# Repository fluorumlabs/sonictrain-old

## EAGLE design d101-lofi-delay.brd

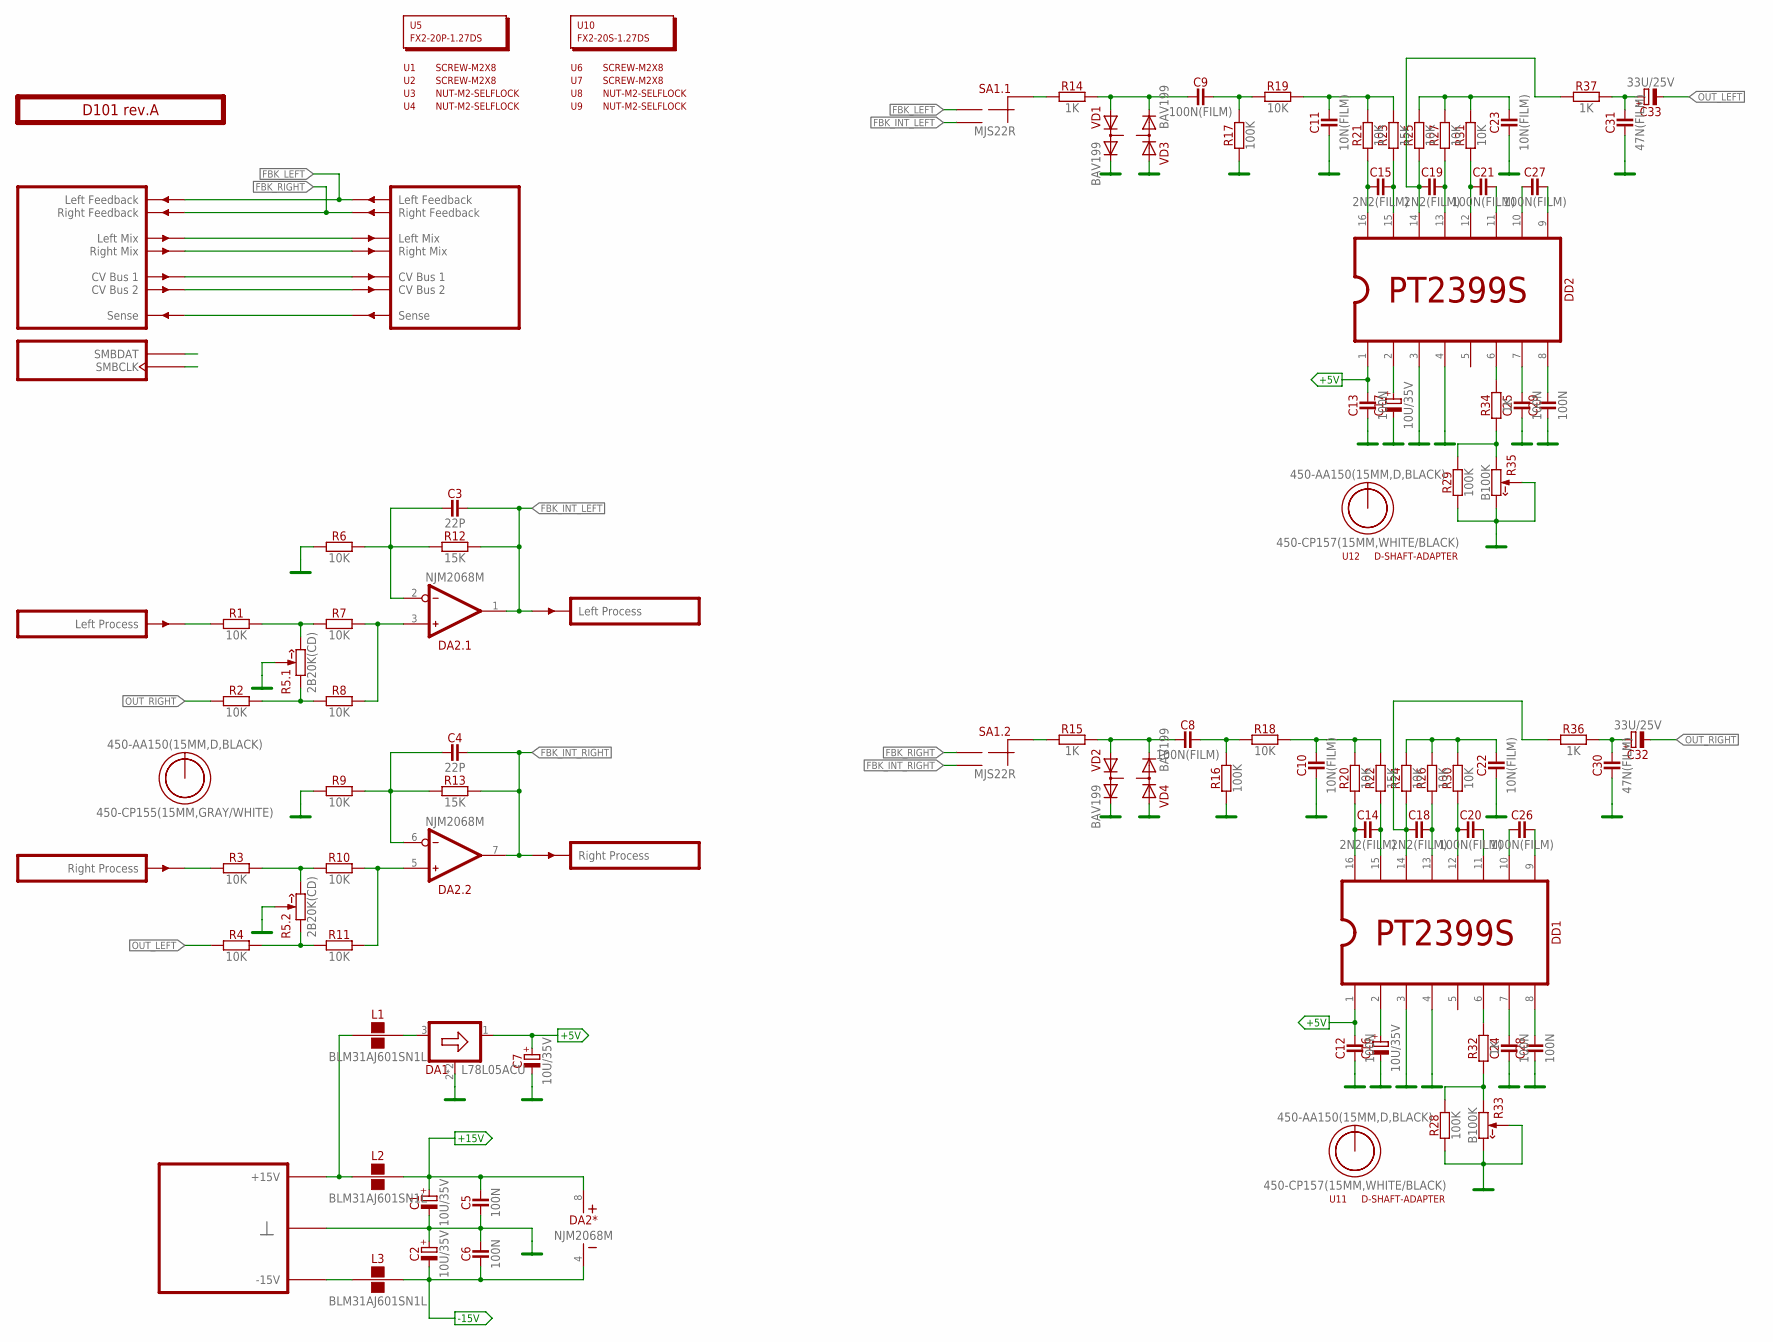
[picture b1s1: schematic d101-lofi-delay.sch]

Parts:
C1, C2, C7, C16, C17: 10U/35V; E2-5
C3, C4: 22P; C-0805
C5, C6, C12, C13, C24, C25, C28, C29: 100N; C-0805
C8, C9, C20, C21, C26, C27: 100N(FILM); C050-025X075
C10, C11, C22, C23: 10N(FILM); C050-025X075
C14, C15, C18, C19: 2N2(FILM); C050-025X075
C30, C31: 47N(FILM); C050-025X075
C32, C33: 33U/25V; E2,5-7
DA1: L78L05ACU; SOT89
DA2: NJM2068M; SO-8
DD1, DD2: PT2399S; SO-16; PARTNO *
L1, L2, L3: BLM31AJ601SN1L; 1206
O1, O3, O5: 450-AA150(15MM,D,BLACK); EMPTY
O2: 450-CP155(15MM,GRAY/WHITE); EMPTY
O4, O6: 450-CP157(15MM,WHITE/BLACK); EMPTY
PCB1: D101 rev.A; ST2-BOARD-50
R1, R2, R3, R4, R6, R7, R8, R9, R10, R11, R18, R19, R20, R21, R24, R25, R26, R27, R30, R31: 10K; R-0805
R5: 2B20K(CD); RV11-DUAL
R12, R13, R22, R23: 15K; R-0805
R14, R15, R32, R34, R36, R37: 1K; R-0805
R16, R17, R28, R29: 100K; R-0805
R33, R35: B100K; RV11-SINGLE
SA1: MJS22R; APEM-MJS22R
U1, U2, U6, U7: SCREW-M2X8; EMPTY
U3, U4, U8, U9: NUT-M2-SELFLOCK; EMPTY
U5: FX2-20P-1.27DS; EMPTY
U10: FX2-20S-1.27DS; EMPTY
U11, U12: D-SHAFT-ADAPTER; EMPTY
VD1, VD2, VD3, VD4: BAV199; SOT23

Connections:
+5V: C7.+, C12.2, C13.2, DA1.1 (OUT), DD1.1, DD2.1
+15V: C1.+, C5.2, DA2.8 (V+), L2.2
-15V: C2.-, C6.1, DA2.4 (V-), L3.2
FBK_INT_LEFT: C3.2, DA2.1 (OUT), PCB1.BOUTL' (OUTL), R12.2, SA1.NO1 (2)
FBK_INT_RIGHT: C4.2, DA2.7 (OUT), PCB1.BOUTR' (OUTR), R13.2, SA1.NO2 (2)
FBK_LEFT: PCB1.ALFBK (LFBK), PCB1.ALFBK' (LFBK'), SA1.NC1 (1)
FBK_RIGHT: PCB1.ARFBK (RFBK), PCB1.ARFBK' (RFBK'), SA1.NC2 (1)
GND: C1.-, C2.+, C5.1, C6.2, C7.-, C10.1, C11.1, C12.1, C13.1, C16.-, C17.-, C22.1, C23.1, C24.1, C25.1, C28.1, C29.1, C30.1, C31.1, DA1.2 (GND), DA1.2@1 (GND), DD1.3, DD1.4, DD2.3, DD2.4, PCB1.B4 (GND), PCB1.B4' (GND), PCB1.B5 (GND), PCB1.B5' (GND), PCB1.B6 (GND), PCB1.B6' (GND), PCB1.B7 (GND), PCB1.B7' (GND), PCB1.B8 (GND), PCB1.B8' (GND), R5.2 (W), R5.2' (W), R6.1, R9.1, R16.1, R17.1, R28.1, R29.1, R33.2 (W), R33.3 (CW), R35.2 (W), R35.3 (CW), VD1.2 (C), VD2.2 (C), VD3.1 (A), VD4.1 (A)
LMIX: PCB1.ALMIX (LMIX), PCB1.ALMIX' (LMIX')
unnamed: R29.2, R34.1, R35.1 (CCW)
unnamed: R28.2, R32.1, R33.1 (CCW)
unnamed: C9.1, R14.2, VD1.1 (A), VD3.2 (C)
unnamed: C15.1, DD2.16, R21.1
unnamed: C8.1, R15.2, VD2.1 (A), VD4.2 (C)
unnamed: R14.1, SA1.C1 (CM)
unnamed: R3.2, R5.3' (CW), R10.1
unnamed: C9.2, R17.2, R19.1
unnamed: C11.2, R19.2, R21.2, R23.2
unnamed: PCB1.BINL (INL), R1.1
unnamed: R15.1, SA1.C2 (CM)
unnamed: C23.2, R25.2, R27.2, R31.2
unnamed: PCB1.BSENSE (SENSE), PCB1.BSENSE' (SENSE')
unnamed: C15.2, DD2.15, R23.1
unnamed: C19.1, DD2.14, R25.1, R37.1
unnamed: C19.2, DD2.13, R27.1
unnamed: C21.1, DD2.12, R31.1
unnamed: C21.2, DD2.11
unnamed: C27.1, DD2.10
unnamed: C27.2, DD2.9
unnamed: C31.2, C33.+, R37.2
unnamed: C4.1, DA2.6 (IN-), R9.2, R13.1
unnamed: PCB1.BINR (INR), R3.1
unnamed: R1.2, R5.3 (CW), R7.1
unnamed: C25.2, DD2.7
unnamed: C29.2, DD2.8
unnamed: DD2.6, R34.2
unnamed: L3.1, PCB1.A-15 (P-15V), PCB1.A-15' (P-15V), PCB1.B-15 (P-15V), PCB1.B-15' (P-15V)
unnamed: C17.+, DD2.2
unnamed: PCB1.ASMBDAT (SMBDAT), PCB1.ASMBDAT' (SMBDAT)
unnamed: DA2.5 (IN+), R10.2, R11.2
unnamed: R4.2, R5.1' (CCW), R11.1
unnamed: PCB1.ACV1 (CV1), PCB1.ACV1' (CV1')
unnamed: PCB1.ACV2 (CV2), PCB1.ACV2' (CV2')
unnamed: PCB1.ASMBCLK (SMBCLK), PCB1.ASMBCLK' (SMBCLK)
unnamed: DA1.3 (IN), L1.2
unnamed: C22.2, R24.2, R26.2, R30.2
unnamed: C14.1, DD1.16, R20.1
unnamed: C14.2, DD1.15, R22.1
unnamed: C18.1, DD1.14, R24.1, R36.1
unnamed: C18.2, DD1.13, R26.1
unnamed: C20.1, DD1.12, R30.1
unnamed: C20.2, DD1.11
unnamed: C26.1, DD1.10
unnamed: C26.2, DD1.9
unnamed: C30.2, C32.+, R36.2
unnamed: C24.2, DD1.7
unnamed: C28.2, DD1.8
unnamed: DD1.6, R32.2
unnamed: DA2.3 (IN+), R7.2, R8.2
unnamed: C8.2, R16.2, R18.1
unnamed: C10.2, R18.2, R20.2, R22.2
unnamed: C3.1, DA2.2 (IN-), R6.2, R12.1
unnamed: R2.2, R5.1 (CCW), R8.1
unnamed: C16.+, DD1.2
OUT_LEFT: C33.-, R4.1
OUT_RIGHT: C32.-, R2.1
P+15V: L1.1, L2.1, PCB1.A+15 (P+15V), PCB1.A+15' (P+15V), PCB1.B+15 (P+15V), PCB1.B+15' (P+15V)
RMIX: PCB1.ARMIX (RMIX), PCB1.ARMIX' (RMIX')

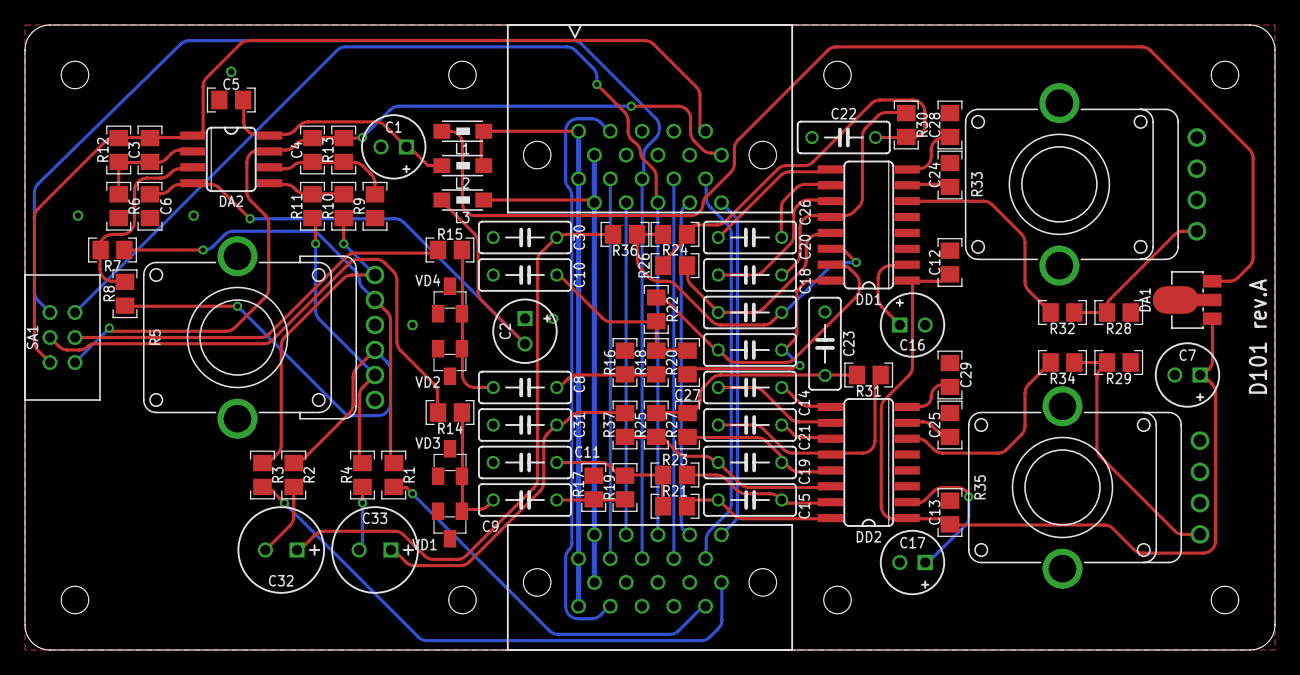
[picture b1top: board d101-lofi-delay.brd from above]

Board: 2 copper layers, 100.0 x 50.0 mm, 101 parts (0 on the bottom side), 68 nets.

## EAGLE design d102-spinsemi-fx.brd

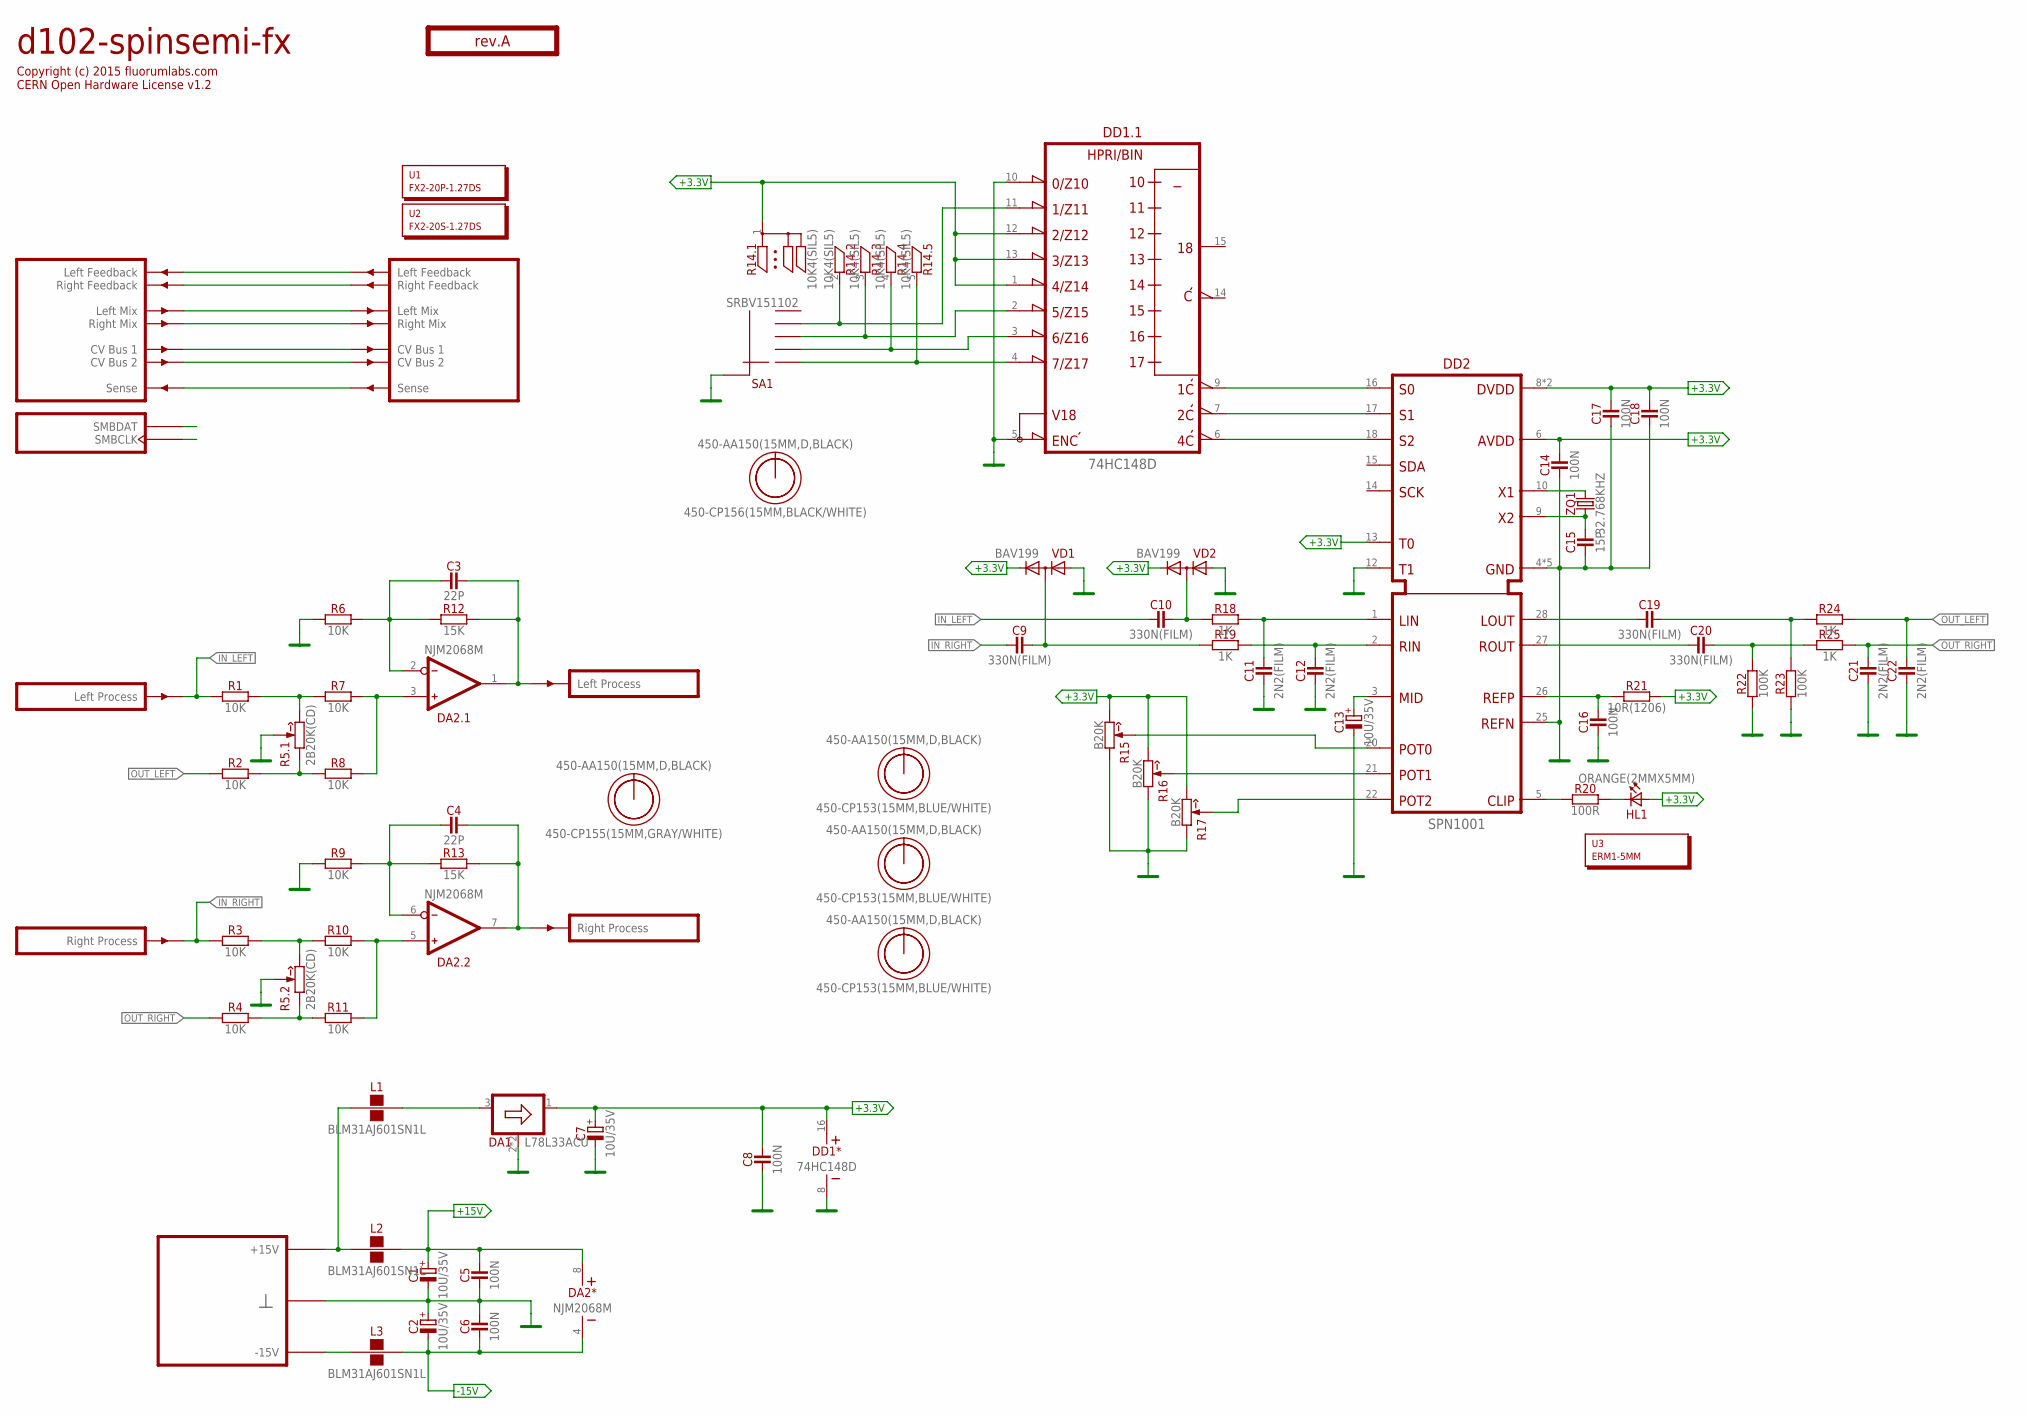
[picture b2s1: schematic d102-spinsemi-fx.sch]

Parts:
C1, C2, C7, C13: 10U/35V; E2-5
C3, C4: 22P; C-0805
C5, C6, C8, C14, C16, C17, C18: 100N; C-0805
C9, C10, C19, C20: 330N(FILM); C050-035X075
C11, C12, C21, C22: 2N2(FILM); C050-025X075
C15: 15P; C-0805
DA1: L78L33ACU; SOT89
DA2: NJM2068M; SO-8
DD1: 74HC148D; SO-16
DD2: SPN1001; SO28W
HL1: ORANGE(2MMX5MM); LED2X5
L1, L2, L3: BLM31AJ601SN1L; 1206
O1: TITLE; EMPTY
O2, O4, O6, O8, O10: 450-AA150(15MM,D,BLACK); EMPTY
O3: 450-CP155(15MM,GRAY/WHITE); EMPTY
O5: 450-CP156(15MM,BLACK/WHITE); EMPTY
O7, O9, O11: 450-CP153(15MM,BLUE/WHITE); EMPTY
PCB1: rev.A; ST2-BOARD-50
R1, R2, R3, R4, R6, R7, R8, R9, R10, R11: 10K; R-0805
R5: 2B20K(CD); RV11-DUAL
R12, R13: 15K; R-0805
R14: 10K4(SIL5); R-SIL5
R15, R16, R17: B20K; RV11-SINGLE
R18, R19, R24, R25: 1K; R-0805
R20: 100R; R-0805
R21: 10R(1206); R-1206
R22, R23: 100K; R-0805
SA1: SRBV151102; SRBV
U1: FX2-20P-1.27DS; EMPTY
U2: FX2-20S-1.27DS; EMPTY
U3: ERM1-5MM; EMPTY
VD1, VD2: BAV199; SOT23
ZQ1: 32.768KHZ; 3215

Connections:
+3.3V: C7.+, C8.2, C14.2, C17.2, C18.2, DA1.1 (OUT), DD1.1 (4), DD1.12 (2), DD1.13 (3), DD1.16 (V+), DD2.6 (AVDD), DD2.8 (DVDD), DD2.13 (T0), DD2.23 (DVDD), HL1.A, R14.1, R15.3 (CW), R16.3 (CW), R17.3 (CW), R21.2, VD1.2 (C), VD2.2 (C)
+15V: C1.+, C5.2, DA2.8 (V+), L2.2
-15V: C2.-, C6.1, DA2.4 (V-), L3.2
GND: C1.-, C2.+, C5.1, C6.2, C7.-, C8.1, C11.1, C12.1, C13.-, C14.1, C15.1, C16.1, C17.1, C18.1, C21.1, C22.1, DA1.2 (GND), DA1.2@1 (GND), DD1.5 (EI), DD1.8 (V-), DD1.10 (0), DD2.4 (GND), DD2.7 (GND), DD2.11 (GND), DD2.12 (T1), DD2.19 (GND), DD2.24 (GND), DD2.25 (REFN), PCB1.B4 (GND), PCB1.B4' (GND), PCB1.B5 (GND), PCB1.B5' (GND), PCB1.B6 (GND), PCB1.B6' (GND), PCB1.B7 (GND), PCB1.B7' (GND), PCB1.B8 (GND), PCB1.B8' (GND), R5.2 (W), R5.2' (W), R6.1, R9.1, R15.1 (CCW), R16.1 (CCW), R17.1 (CCW), R22.1, R23.1, SA1.1 (CM), SA1.10 (CM), VD1.1 (A), VD2.1 (A)
IN_LEFT: C10.1, PCB1.BINL (INL), R1.1
IN_RIGHT: C9.1, PCB1.BINR (INR), R3.1
LMIX: PCB1.ALMIX (LMIX), PCB1.ALMIX' (LMIX')
unnamed: PCB1.ALFBK (LFBK), PCB1.ALFBK' (LFBK')
unnamed: PCB1.ARFBK (RFBK), PCB1.ARFBK' (RFBK')
unnamed: C3.2, DA2.1 (OUT), PCB1.BOUTL' (OUTL), R12.2
unnamed: C4.2, DA2.7 (OUT), PCB1.BOUTR' (OUTR), R13.2
unnamed: DD1.4 (7), R14.5, SA1.2 (1)
unnamed: DD1.3 (6), R14.4, SA1.3 (2)
unnamed: R3.2, R5.3' (CW), R10.1
unnamed: DD1.2 (5), R14.3, SA1.4 (3)
unnamed: DD1.11 (1), R14.2, SA1.5 (4)
unnamed: DD1.9 (A0), DD2.16 (S0)
unnamed: DD2.10 (X1), ZQ1.2
unnamed: DD1.7 (A1), DD2.17 (S1)
unnamed: DD1.6 (A2), DD2.18 (S2)
unnamed: HL1.K (C), R20.2
unnamed: DD2.5 (CLIP), R20.1
unnamed: PCB1.BSENSE (SENSE), PCB1.BSENSE' (SENSE')
unnamed: C12.2, DD2.2 (RIN), R19.2
unnamed: DD2.22 (POT2), R17.2 (W)
unnamed: DD2.21 (POT1), R16.2 (W)
unnamed: DD2.20 (POT0), R15.2 (W)
unnamed: C16.2, DD2.26 (REFP), R21.1
unnamed: C13.+, DD2.3 (MID)
unnamed: C11.2, DD2.1 (LIN), R18.2
unnamed: C10.2, R18.1, VD2.3 (CMN)
unnamed: C4.1, DA2.6 (IN-), R9.2, R13.1
unnamed: C9.2, R19.1, VD1.3 (CMN)
unnamed: C19.1, DD2.28 (LOUT)
unnamed: C15.2, DD2.9 (X2), ZQ1.1
unnamed: C20.1, DD2.27 (ROUT)
unnamed: R1.2, R5.3 (CW), R7.1
unnamed: C20.2, R22.2, R25.1
unnamed: C19.2, R23.2, R24.1
unnamed: L3.1, PCB1.A-15 (P-15V), PCB1.A-15' (P-15V), PCB1.B-15 (P-15V), PCB1.B-15' (P-15V)
unnamed: PCB1.ASMBDAT (SMBDAT), PCB1.ASMBDAT' (SMBDAT)
unnamed: DA2.5 (IN+), R10.2, R11.2
unnamed: R4.2, R5.1' (CCW), R11.1
unnamed: PCB1.ACV1 (CV1), PCB1.ACV1' (CV1')
unnamed: PCB1.ACV2 (CV2), PCB1.ACV2' (CV2')
unnamed: PCB1.ASMBCLK (SMBCLK), PCB1.ASMBCLK' (SMBCLK)
unnamed: DA1.3 (IN), L1.2
unnamed: DA2.3 (IN+), R7.2, R8.2
unnamed: C3.1, DA2.2 (IN-), R6.2, R12.1
unnamed: R2.2, R5.1 (CCW), R8.1
OUT_LEFT: C22.2, R2.1, R24.2
OUT_RIGHT: C21.2, R4.1, R25.2
P+15V: L1.1, L2.1, PCB1.A+15 (P+15V), PCB1.A+15' (P+15V), PCB1.B+15 (P+15V), PCB1.B+15' (P+15V)
RMIX: PCB1.ARMIX (RMIX), PCB1.ARMIX' (RMIX')

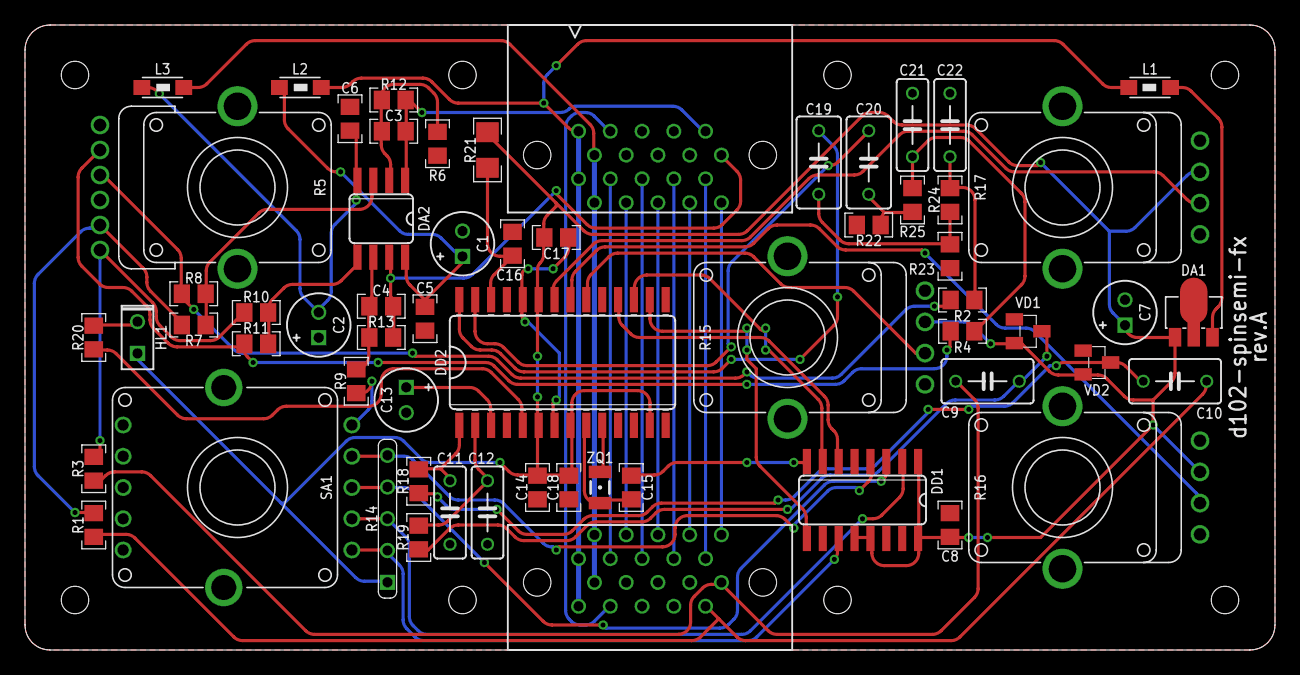
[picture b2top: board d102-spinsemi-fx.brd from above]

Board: 2 copper layers, 100.0 x 50.0 mm, 74 parts (0 on the bottom side), 54 nets.

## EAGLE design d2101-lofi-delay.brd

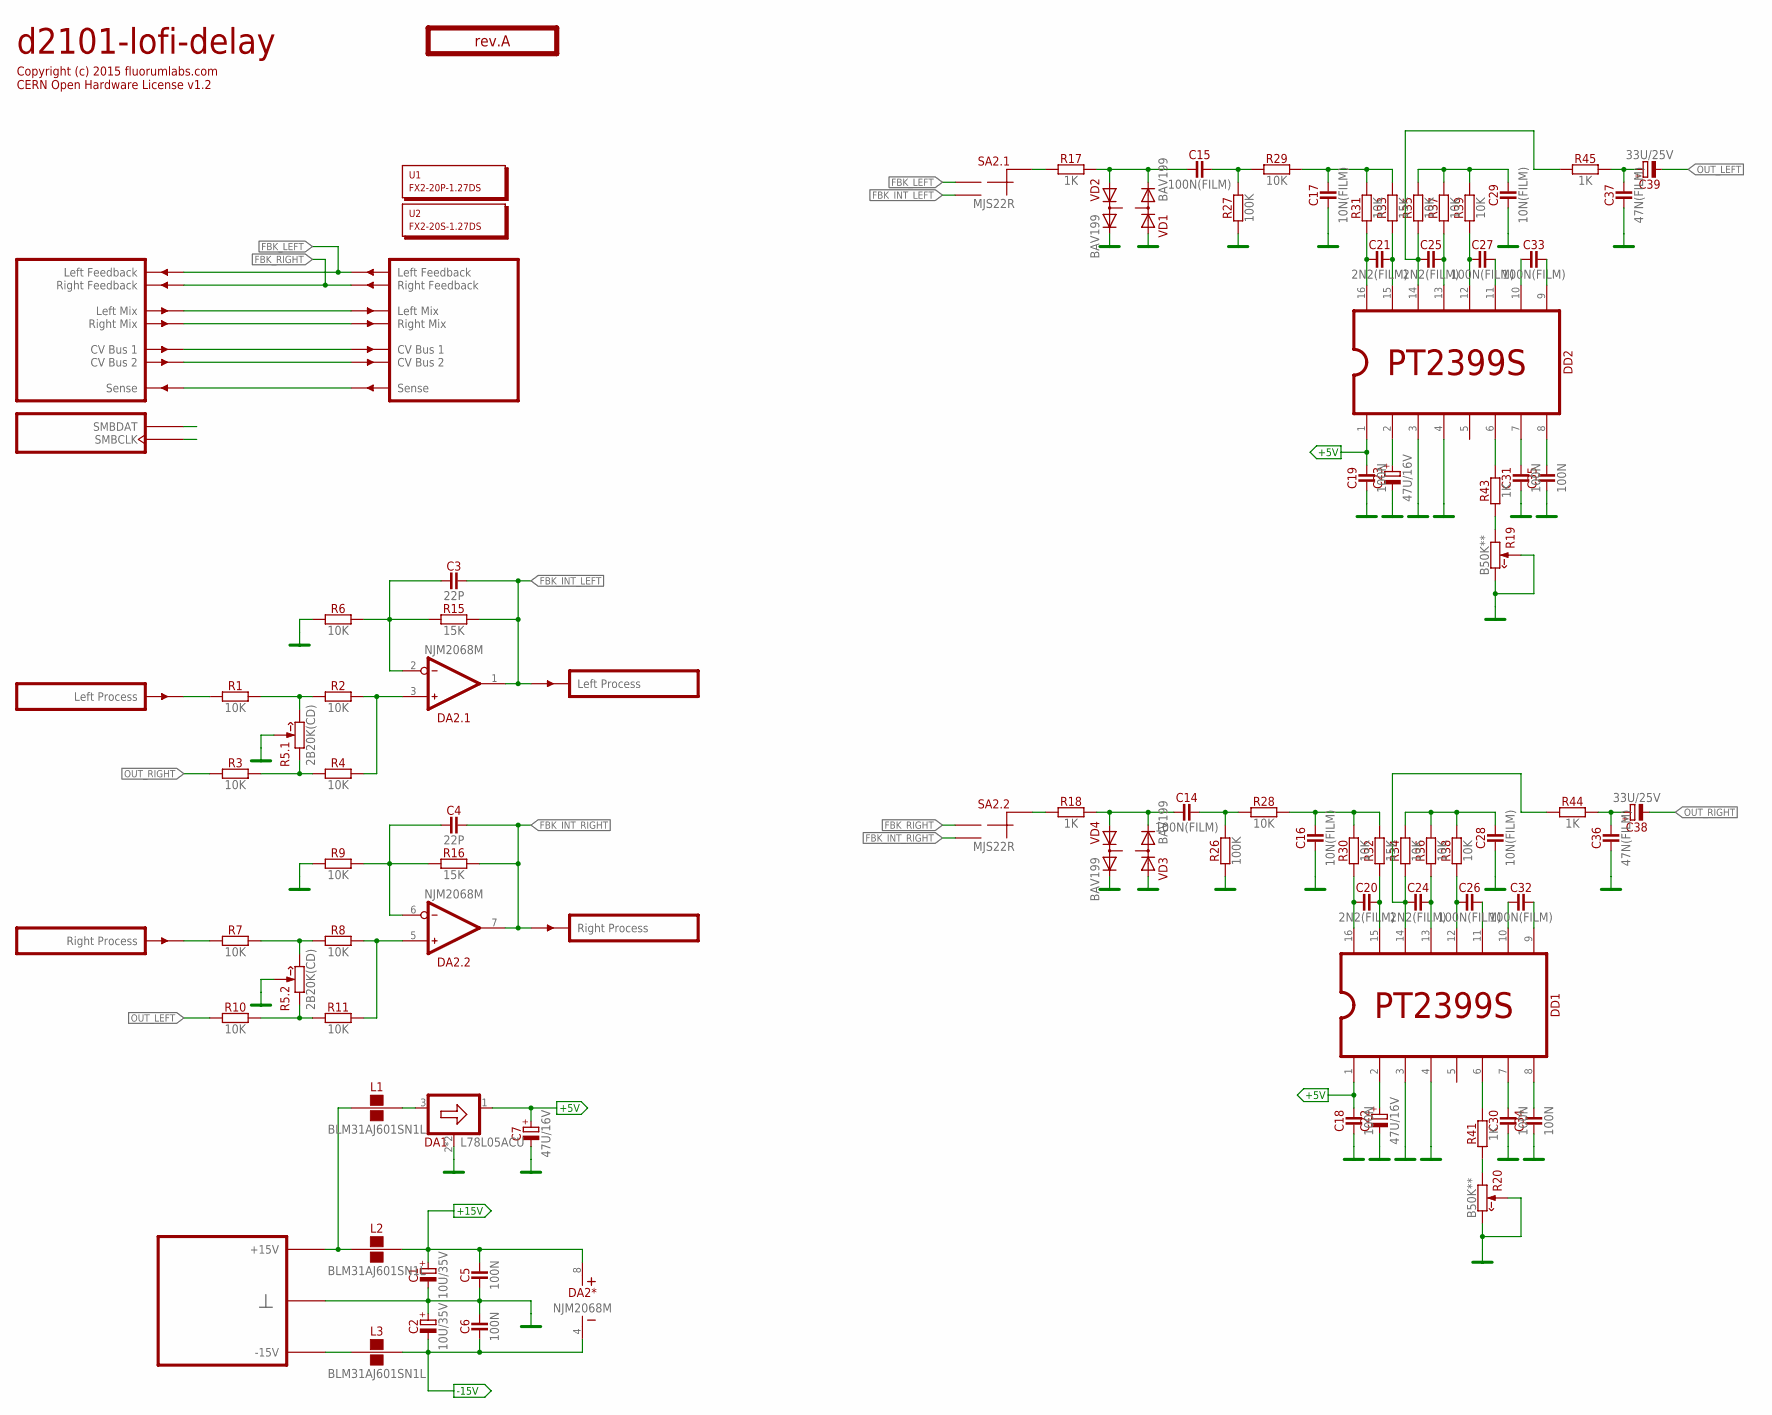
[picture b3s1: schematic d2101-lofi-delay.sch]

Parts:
C1, C2: 10U/35V; E2-5
C3, C4: 22P; C-0805
C5, C6, C18, C19, C30, C31, C34, C35: 100N; C-0805
C7, C22, C23: 47U/16V; E2-5
C14, C15, C26, C27, C32, C33: 100N(FILM); C050-025X075
C16, C17, C28, C29: 10N(FILM); C050-025X075
C20, C21, C24, C25: 2N2(FILM); C050-025X075
C36, C37: 47N(FILM); C050-025X075
C38, C39: 33U/25V; E2,5-7
DA1: L78L05ACU; SOT89
DA2: NJM2068M; SO-8
DD1, DD2: PT2399S; SO-16; PARTNO *
L1, L2, L3: BLM31AJ601SN1L; 1206
O1: TITLE; EMPTY
PCB1: rev.A; ST2-BOARD-50
R1, R2, R3, R4, R6, R7, R8, R9, R10, R11, R28, R29, R30, R31, R34, R35, R36, R37, R38, R39: 10K; R-0805
R5: 2B20K(CD); RV11-DUAL
R15, R16, R32, R33: 15K; R-0805
R17, R18, R41, R43, R44, R45: 1K; R-0805
R19, R20: B50K**; RV11-SINGLE
R26, R27: 100K; R-0805
SA2: MJS22R; APEM-MJS22R
U1: FX2-20P-1.27DS; EMPTY
U2: FX2-20S-1.27DS; EMPTY
VD1, VD2, VD3, VD4: BAV199; SOT23

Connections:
+5V: C7.+, C18.2, C19.2, DA1.1 (OUT), DD1.1, DD2.1
+15V: C1.+, C5.2, DA2.8 (V+), L2.2
-15V: C2.-, C6.1, DA2.4 (V-), L3.2
FBK_INT_LEFT: C3.2, DA2.1 (OUT), PCB1.BOUTL' (OUTL), R15.2, SA2.NO1 (2)
FBK_INT_RIGHT: C4.2, DA2.7 (OUT), PCB1.BOUTR' (OUTR), R16.2, SA2.NO2 (2)
FBK_LEFT: PCB1.ALFBK (LFBK), PCB1.ALFBK' (LFBK'), SA2.NC1 (1)
FBK_RIGHT: PCB1.ARFBK (RFBK), PCB1.ARFBK' (RFBK'), SA2.NC2 (1)
GND: C1.-, C2.+, C5.1, C6.2, C7.-, C16.1, C17.1, C18.1, C19.1, C22.-, C23.-, C28.1, C29.1, C30.1, C31.1, C34.1, C35.1, C36.1, C37.1, DA1.2 (GND), DA1.2@1 (GND), DD1.3, DD1.4, DD2.3, DD2.4, PCB1.B4 (GND), PCB1.B4' (GND), PCB1.B5 (GND), PCB1.B5' (GND), PCB1.B6 (GND), PCB1.B6' (GND), PCB1.B7 (GND), PCB1.B7' (GND), PCB1.B8 (GND), PCB1.B8' (GND), R5.2 (W), R5.2' (W), R6.1, R9.1, R19.2 (W), R19.3 (CW), R20.2 (W), R20.3 (CW), R26.1, R27.1, VD1.1 (A), VD2.2 (C), VD3.1 (A), VD4.2 (C)
LMIX: PCB1.ALMIX (LMIX), PCB1.ALMIX' (LMIX')
unnamed: R19.1 (CCW), R43.1
unnamed: R20.1 (CCW), R41.1
unnamed: C15.1, R17.2, VD1.2 (C), VD2.1 (A)
unnamed: C21.1, DD2.16, R31.1
unnamed: C14.1, R18.2, VD3.2 (C), VD4.1 (A)
unnamed: R17.1, SA2.C1 (CM)
unnamed: R5.3' (CW), R7.2, R8.1
unnamed: C15.2, R27.2, R29.1
unnamed: C17.2, R29.2, R31.2, R33.2
unnamed: PCB1.BINL (INL), R1.1
unnamed: R18.1, SA2.C2 (CM)
unnamed: C29.2, R35.2, R37.2, R39.2
unnamed: PCB1.BSENSE (SENSE), PCB1.BSENSE' (SENSE')
unnamed: C21.2, DD2.15, R33.1
unnamed: C25.1, DD2.14, R35.1, R45.1
unnamed: C25.2, DD2.13, R37.1
unnamed: C27.1, DD2.12, R39.1
unnamed: C27.2, DD2.11
unnamed: C33.1, DD2.10
unnamed: C33.2, DD2.9
unnamed: C37.2, C39.+, R45.2
unnamed: C4.1, DA2.6 (IN-), R9.2, R16.1
unnamed: PCB1.BINR (INR), R7.1
unnamed: R1.2, R2.1, R5.3 (CW)
unnamed: C31.2, DD2.7
unnamed: C35.2, DD2.8
unnamed: DD2.6, R43.2
unnamed: L3.1, PCB1.A-15 (P-15V), PCB1.A-15' (P-15V), PCB1.B-15 (P-15V), PCB1.B-15' (P-15V)
unnamed: C23.+, DD2.2
unnamed: PCB1.ASMBDAT (SMBDAT), PCB1.ASMBDAT' (SMBDAT)
unnamed: DA2.5 (IN+), R8.2, R11.2
unnamed: R5.1' (CCW), R10.2, R11.1
unnamed: PCB1.ACV1 (CV1), PCB1.ACV1' (CV1')
unnamed: PCB1.ACV2 (CV2), PCB1.ACV2' (CV2')
unnamed: PCB1.ASMBCLK (SMBCLK), PCB1.ASMBCLK' (SMBCLK)
unnamed: DA1.3 (IN), L1.2
unnamed: C28.2, R34.2, R36.2, R38.2
unnamed: C20.1, DD1.16, R30.1
unnamed: C20.2, DD1.15, R32.1
unnamed: C24.1, DD1.14, R34.1, R44.1
unnamed: C24.2, DD1.13, R36.1
unnamed: C26.1, DD1.12, R38.1
unnamed: C26.2, DD1.11
unnamed: C32.1, DD1.10
unnamed: C32.2, DD1.9
unnamed: C36.2, C38.+, R44.2
unnamed: C30.2, DD1.7
unnamed: C34.2, DD1.8
unnamed: DD1.6, R41.2
unnamed: DA2.3 (IN+), R2.2, R4.2
unnamed: C14.2, R26.2, R28.1
unnamed: C16.2, R28.2, R30.2, R32.2
unnamed: C3.1, DA2.2 (IN-), R6.2, R15.1
unnamed: R3.2, R4.1, R5.1 (CCW)
unnamed: C22.+, DD1.2
OUT_LEFT: C39.-, R10.1
OUT_RIGHT: C38.-, R3.1
P+15V: L1.1, L2.1, PCB1.A+15 (P+15V), PCB1.A+15' (P+15V), PCB1.B+15 (P+15V), PCB1.B+15' (P+15V)
RMIX: PCB1.ARMIX (RMIX), PCB1.ARMIX' (RMIX')

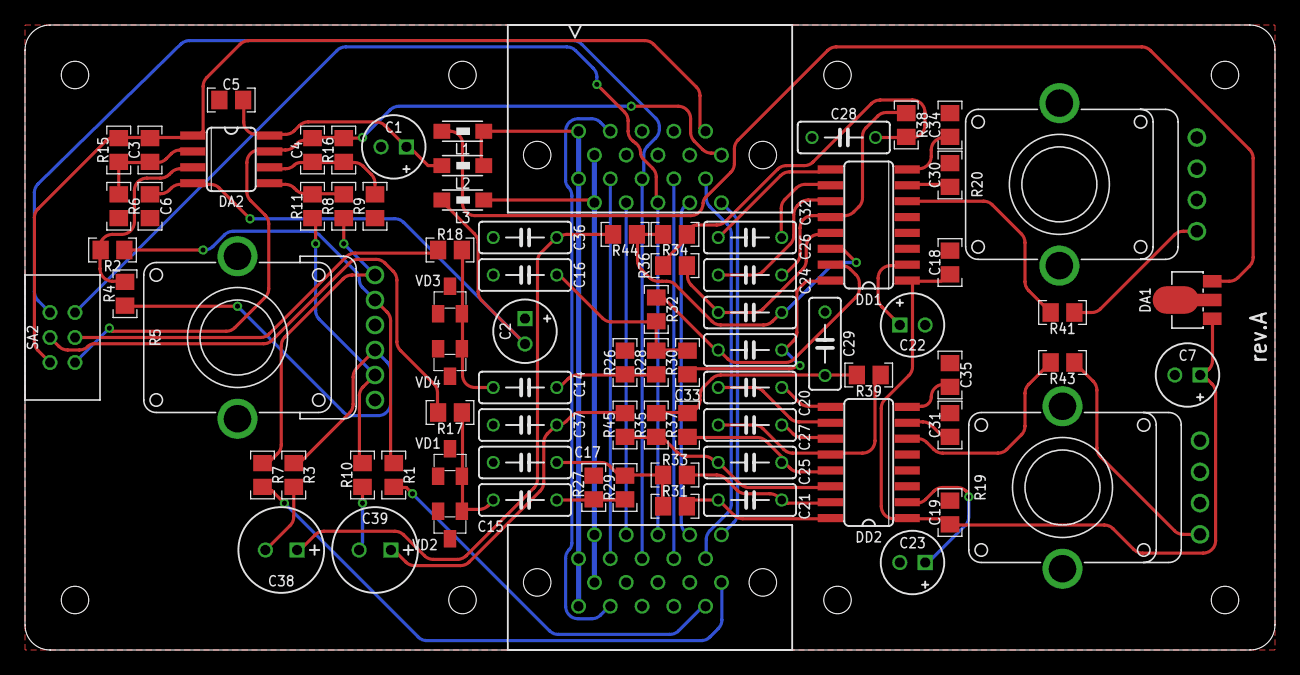
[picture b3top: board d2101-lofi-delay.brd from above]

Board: 2 copper layers, 100.0 x 50.0 mm, 84 parts (0 on the bottom side), 68 nets.

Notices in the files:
parts and their libraries:
text: Copyright (c) 2015 fluorumlabs.com
CERN Open Hardware License v1.2
